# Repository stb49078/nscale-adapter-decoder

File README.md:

# Lokdecoder - Adapter Platinen und DIY Decoder - Spur N

Hier finden sich div. Adapterplatinen und vollständige DIY Lokdecoder auf Basis des (vermutlich eingestellten)
Projekts [Aegaeon](https://github.com/Railstars/Aegaeon) von [Railstars](http://railstars.com/).

Wie dieses Projekt auch, stehen die hier veröffentlichten Designs damit automatisch unter GPLv3.

Die Dekoder wurden leicht angeändert, und verwenden den Motortreiber
[BD623xx](http://rohmfs.rohm.com/en/products/databook/datasheet/ic/motor/dc/bd623x-e.pdf).

## Arnold

**1020/E94**

[NEM-651 Adapter](./loc-decoder/Arnold/1020/NEM-651_Adapter)

## Roco

**1044 alt, z.B. 23242**

[NEM-651 Adapter](./loc-decoder/Roco/1044/NEM-651_Adapter)

[Aegaeon Decoder mit BD62xx und Railcom](./loc-decoder/Roco/1044/Decoder-BD62xx-Railcom)

**BR215, z.B. 2150B**

[NEM-651 Adapter](./loc-decoder/Roco/BR215/NEM-651_Adapter)

**BR 44, z.B. 2106B**

[NEM-651 Adapter](./loc-decoder/Roco/BR44/NEM-651_Adapter)

## Minitrix

**E44**

[NEM-651 Adapter](./loc-decoder/Minitrix/E44/NEM-651_Adapter)

## Spectrum

**GE Dash 8-40CW**

[Aegaeon Decoder mit BD62xx und Railcom](./loc-decoder/Spectrum/GE_Dash_8-40CW/Decoder-BD62xx-Railcom)

# Wagonbeleuchtung mit integriertem Decoder- Spur N

Mit freundlicher Erlaubnis von Hr. Brandt, verwende ich als Basis
für die Wagonbeleuchtung, seinen unter https://www.digital-bahn.de/bau_wald/wald_2v1.htm
veröffentlicheten Spur H0 - Waggon-Licht Dekoder (WaLD) V2.1
Sämtliche Lizenzen für diese Platinen und der darauf verwendeten Software liegen bei digital-bahn.

Diese Platinen werden von meiner Seite nicht zum Verkauf angeboten.
Der Verkauf und/oder Vertrieb eines hier veröffentlichten Designs darf nur unter
Rücksprache mit digital-bahn erfolgen. Copyleft.

Die Anleitung zur Installation der Software und die Schaltungsbeschreibung sind
in der oben genannten Seite zu finden.

Die originale H0-Platine und vorprogrammierte PIC-Controller können im Shop von
digital-bahn unter https://digital-bahn.de/shopping/Waggon-Beleuchtung bezogen werden.  

Folgende Modelle werden aktuell unterstützt:

[Roco - Eurofima z.B. 24270, 24285, uvm.](./wagon-light/Roco/Eurofima)

[Roco - Eilzugwagen / Schlierenwagen z.B. 24280-24281 ](./wagon-light/Roco/Eilzugwagen)

[Minitrix - Eurofima z.B. 3095, 3106, uvm.](./wagon-light/Minitrix/Eurofima)

Für kleinere Wägen gibt es allgemeine Platinen

[Einseite Montage - 50mm * 15mm](./wagon-light/common/50x15)

## Support und Fragen

Bei Fragen, Anregungen und Beschwerden, bitte einfach unter spur.n@stefanbauer.at melden.

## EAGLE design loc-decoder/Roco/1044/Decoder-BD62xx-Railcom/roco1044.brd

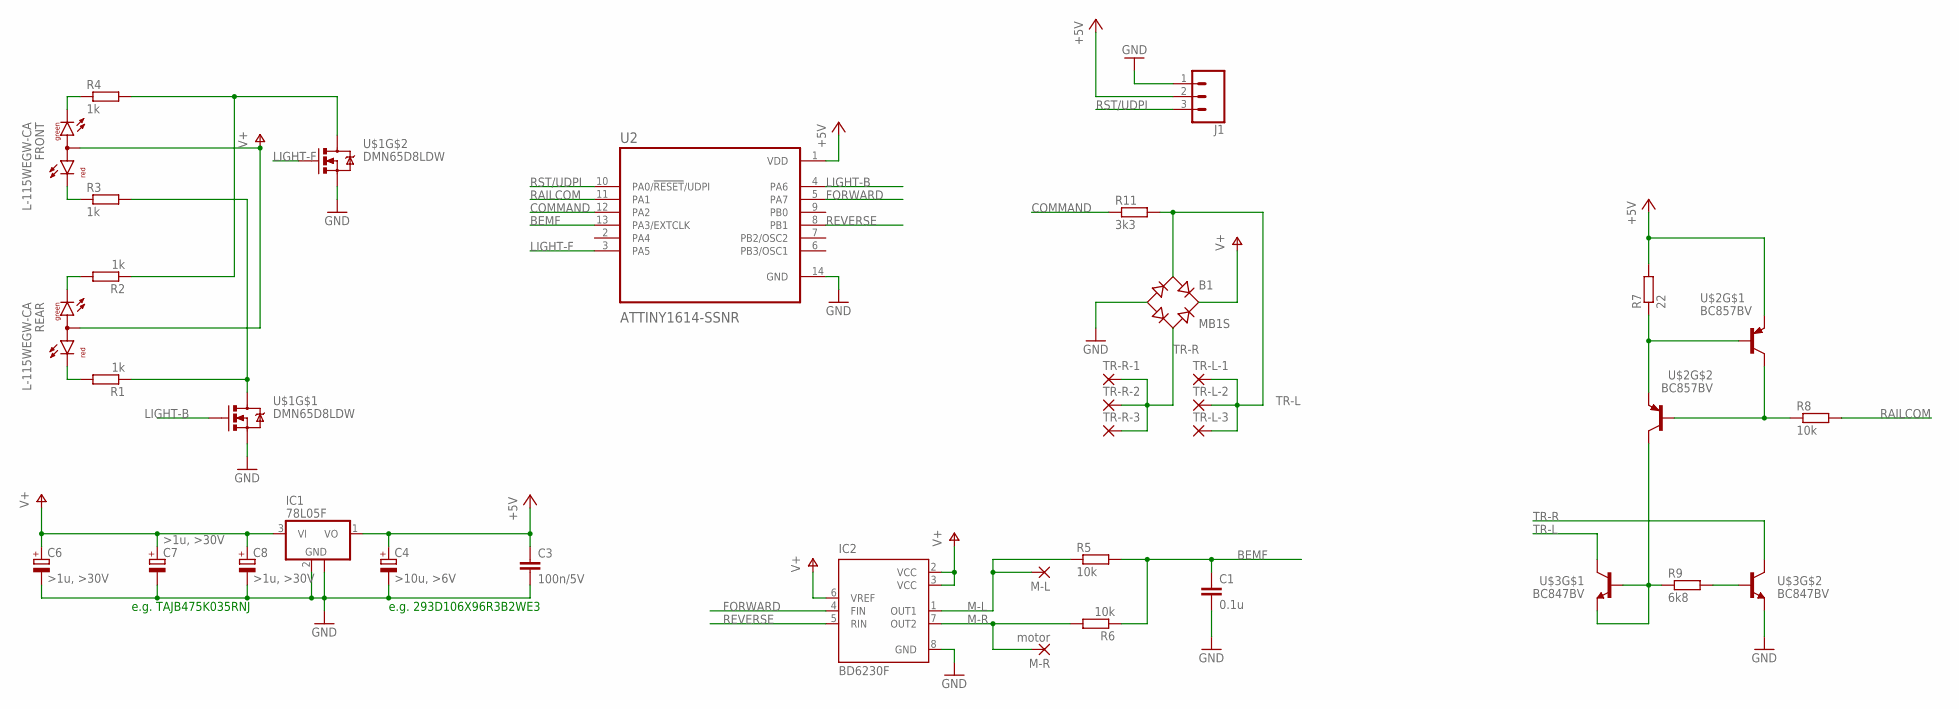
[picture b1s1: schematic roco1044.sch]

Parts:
B1: MB1S; SOIC-4
C1: 0.1u; C0805
C3: 100n/5V; C0805
C4: >10u, >6V; CT3528
C6, C7, C8: >1u, >30V; CT3528
FRONT: L-115WEGW-CA; DUOLED-A-3MM
IC1: 78L05F; SOT89
IC2: BD6230F; SOP8
J1: 455-1750-1-ND; 1X03
M-L: SMD5; SMD2,54-5,08
M-R: motor; SMD2,54-5,08
R1, R2, R3, R4: 1k; R0805
R5, R6, R8: 10k; R0805
R7: 22; R0805
R9: 6k8; R0805
R11: 3k3; R0805
REAR: L-115WEGW-CA; DUOLED-A-3MM
TR-L-1, TR-L-2, TR-L-3: SMD5; SMD2,54-5,08
TR-R-1, TR-R-2, TR-R-3: SMD5; SMD2,54-5,08
U2: ATTINY1614-SSNR; SOIC127P600X175-14N
U$1: DMN65D8LDW; SOT363
U$2: BC857BV; SOT-666
U$3: BC847BV; SOT-666

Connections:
+5V: C3.1, C4.+, IC1.1 (VO), J1.2, R7.2, U2.1 (VDD), U$2.P$1 (E)
BEMF: C1.1, R5.2, R6.1, U2.13 (PA3/EXTCLK)
COMMAND: R11.1, U2.12 (PA2)
FORWARD: IC2.4 (FIN), U2.5 (PA7)
GND: B1.-, C1.2, C3.2, C4.-, C6.-, C7.-, C8.-, IC1.2 (GND), IC1.2@1 (GND), IC2.8 (GND), J1.1, U2.14 (GND), U$1.P$3 (S), U$1.P$6 (S), U$3.P$4 (E)
LIGHT-B: U2.4 (PA6), U$1.P$2 (G)
LIGHT-F: U2.3 (PA5), U$1.P$5 (G)
M-L: IC2.1 (OUT1), M-L.1, R5.1
M-R: IC2.7 (OUT2), M-R.1, R6.2
unnamed: R9.2, U$3.P$5 (B)
unnamed: R9.1, U$2.P$3 (C), U$3.P$1 (E), U$3.P$2 (B)
unnamed: R2.1, R4.2, U$1.P$1 (D)
unnamed: R1.2, REAR.3 (CR)
unnamed: R2.2, REAR.1 (CG)
unnamed: R1.1, R3.2, U$1.P$4 (D)
unnamed: FRONT.3 (CR), R3.1
unnamed: FRONT.1 (CG), R4.1
unnamed: R7.1, U$2.P$2 (B), U$2.P$4 (E)
unnamed: R8.1, U$2.P$5 (B), U$2.P$6 (C)
RAILCOM: R8.2, U2.11 (PA1)
REVERSE: IC2.5 (RIN), U2.8 (PB1)
RST/UDPI: J1.3, U2.10 (PA0/!RESET!/UDPI)
TR-L: B1.~1 (AC1), R11.2, TR-L-1.1, TR-L-2.1, TR-L-3.1, U$3.P$6 (C)
TR-R: B1.~2 (AC2), TR-R-1.1, TR-R-2.1, TR-R-3.1, U$3.P$3 (C)
V+: B1.+, C6.+, C7.+, C8.+, FRONT.2 (A), IC1.3 (VI), IC2.2 (VCC), IC2.3 (VCC), IC2.6 (VREF), REAR.2 (A)

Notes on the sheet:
e.g. TAJB475K035RNJ
e.g. 293D106X96R3B2WE3

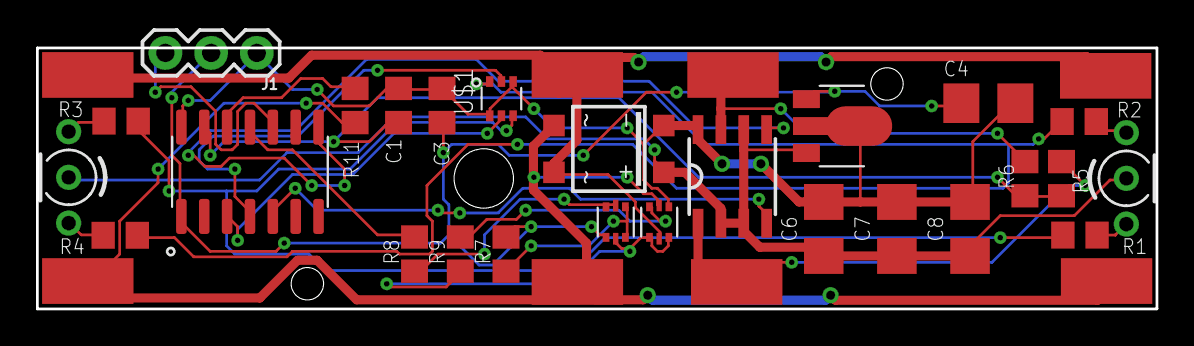
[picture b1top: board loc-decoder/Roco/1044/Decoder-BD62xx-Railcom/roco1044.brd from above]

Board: 2 copper layers, 62.2 x 14.5 mm, 34 parts (0 on the bottom side), 25 nets.

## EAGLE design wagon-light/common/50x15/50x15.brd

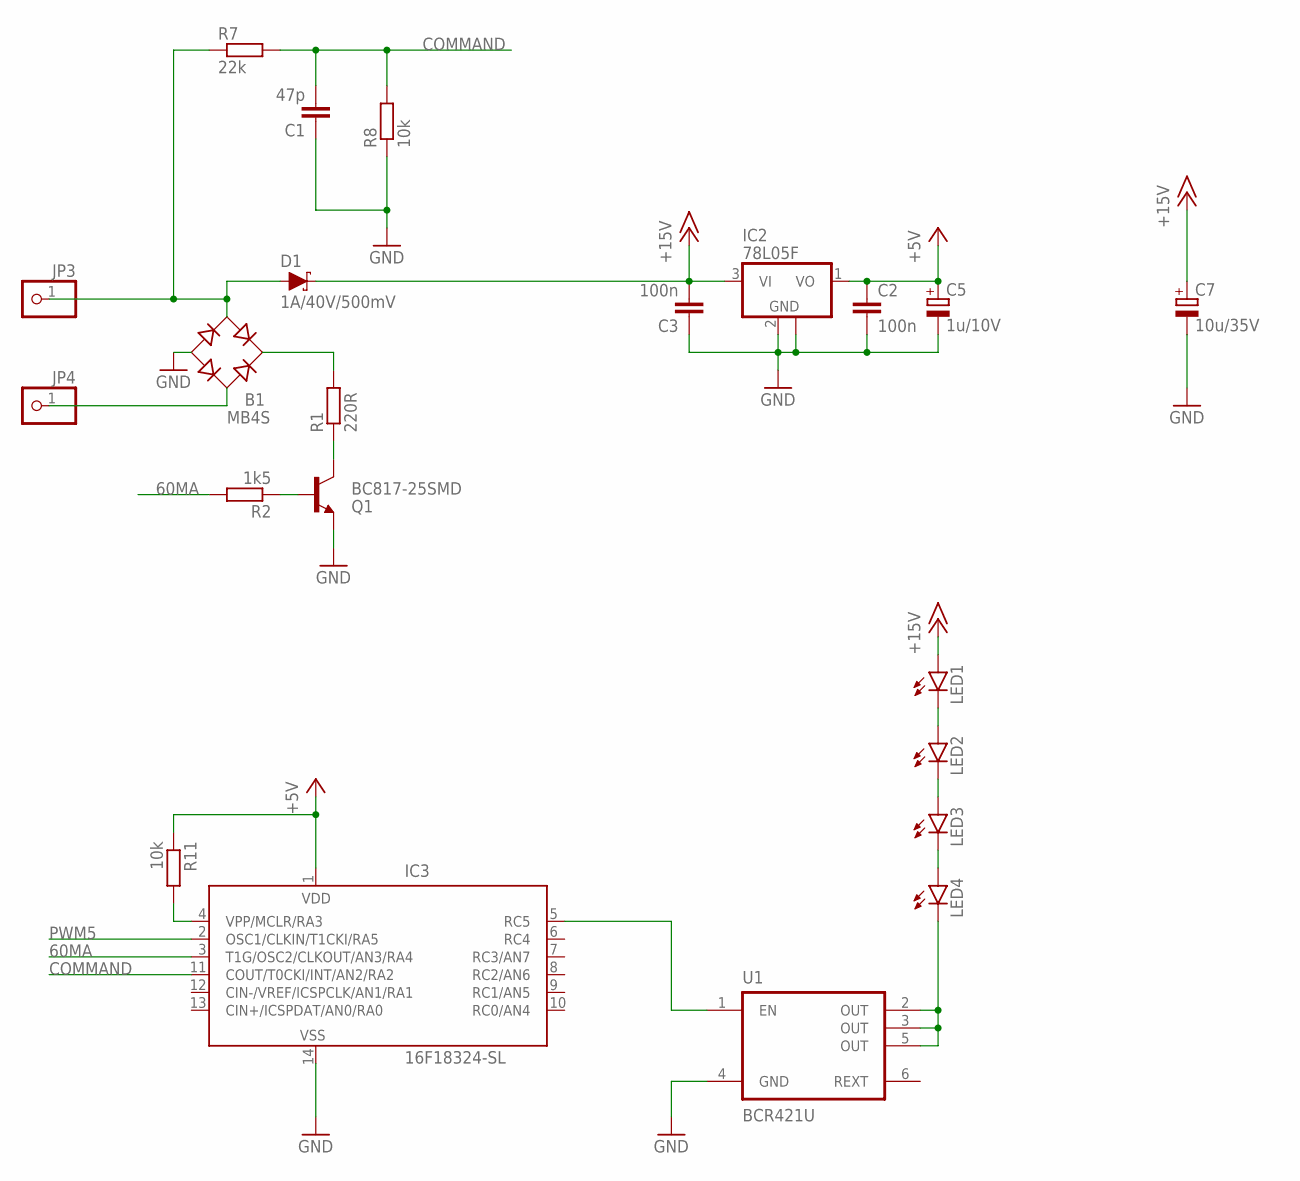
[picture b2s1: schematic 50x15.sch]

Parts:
B1: MB4S; SOIC-4
C1: 47p; C0805
C2, C3: 100n; C3216
C5: 1u/10V; A/3216-18R
C7: 10u/35V; D/7343-31R
D1: 1A/40V/500mV; SMA-DIODE
IC2: 78L05F; SOT89
IC3: 16F18324-SL; SO-14
JP3, JP4: PINHD-1X1; 1X01
LED1, LED2, LED3, LED4: LEDKA-3528ASYC; KA-3528ASYC
Q1: BC817-25SMD; SOT23-BEC
R1: 220R; R1206
R2: 1k5; R1206
R7: 22k; R1206
R8, R11: 10k; R1206
U1: BCR421U; SC74-6

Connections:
60MA: IC3.3 (T1G/OSC2/CLKOUT/AN3/RA4), R2.2
+5V: C2.1, C5.+, IC2.1 (VO), IC3.1 (VDD), R11.1
+15V: C3.2, C7.+, D1.C, IC2.3 (VI), LED1.A
COMMAND: C1.2, IC3.11 (COUT/T0CKI/INT/AN2/RA2), R7.2, R8.2
GND: B1.-, C1.1, C2.2, C3.1, C5.-, C7.-, IC2.2 (GND), IC2.2@1 (GND), IC3.14 (VSS), Q1.E, R8.1, U1.4 (GND)
unnamed: B1.~2 (AC2), JP4.1
unnamed: B1.~1 (AC1), D1.A, JP3.1, R7.1
unnamed: Q1.C, R1.1
unnamed: Q1.B, R2.1
unnamed: B1.+, R1.2
unnamed: IC3.5 (RC5), U1.1 (EN)
unnamed: LED4.C, U1.2 (OUT), U1.3 (OUT), U1.5 (OUT)
unnamed: LED3.C, LED4.A
unnamed: LED2.C, LED3.A
unnamed: LED1.C, LED2.A
unnamed: IC3.4 (VPP/MCLR/RA3), R11.2
PWM5: IC3.2 (OSC1/CLKIN/T1CKI/RA5)

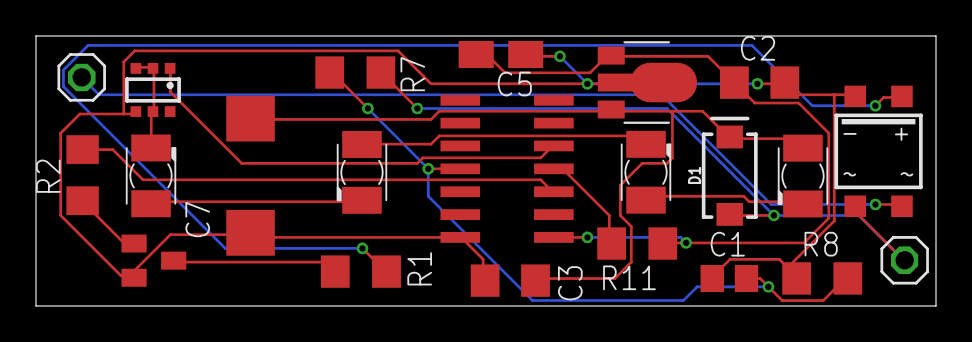
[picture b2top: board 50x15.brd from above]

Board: 2 copper layers, 50.0 x 15.0 mm, 22 parts (0 on the bottom side), 16 nets.

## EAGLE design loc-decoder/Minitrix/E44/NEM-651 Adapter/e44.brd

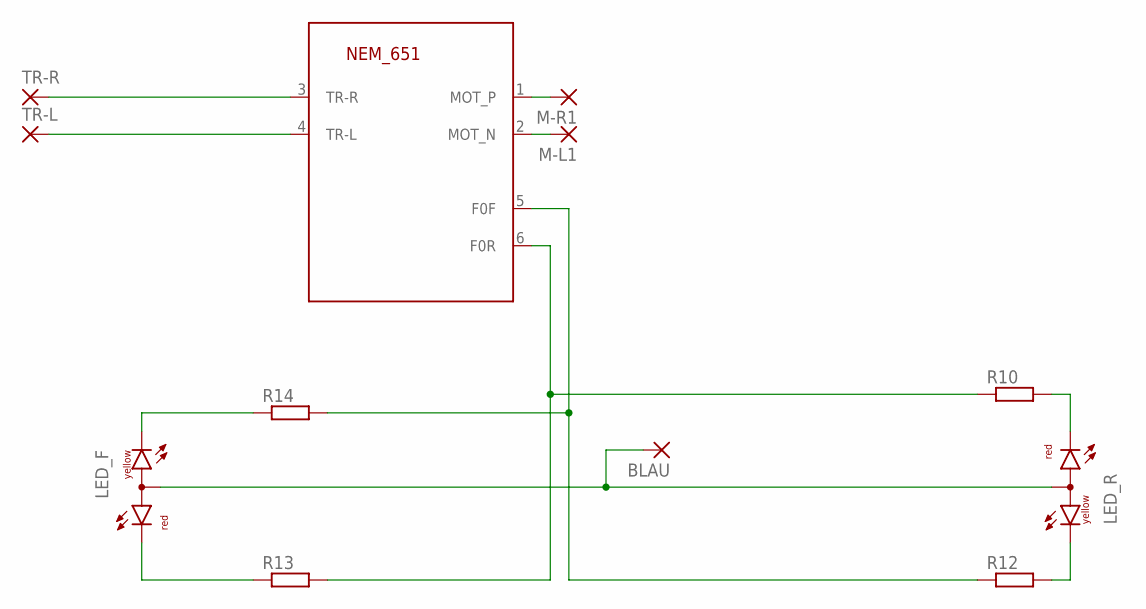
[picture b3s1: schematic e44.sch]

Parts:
651: NEM_651-TS; 53047-06
BLAU: 1,6/0,8
LED_F: DUOLED-RY-A; DUOLED-A-5MM
LED_R: DUOLED-RY-A; DUOLED-A-5MM
M-L1: SMD5; SMD2,54-5,08
M-R1: SMD5; SMD2,54-5,08
R10, R12, R13, R14: R-EU_R1206; R1206
TR-L: SMD5; SMD2,54-5,08
TR-R: SMD5; SMD2,54-5,08

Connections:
unnamed: BLAU.1, LED_F.A, LED_R.A
unnamed: 651.4 (TR-L), TR-L.1
unnamed: 651.3 (TR-R), TR-R.1
unnamed: 651.5 (F0F), R12.1, R14.2
unnamed: LED_R.CR, R10.2
unnamed: LED_R.CX (CY), R12.2
unnamed: 651.6 (F0R), R10.1, R13.2
unnamed: LED_F.CR, R13.1
unnamed: LED_F.CX (CY), R14.1
unnamed: 651.1 (MOT_P), M-R1.1
unnamed: 651.2 (MOT_N), M-L1.1

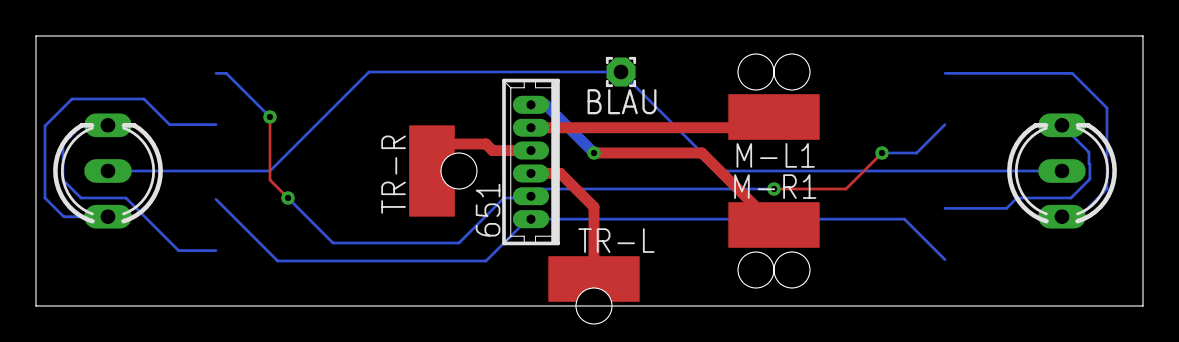
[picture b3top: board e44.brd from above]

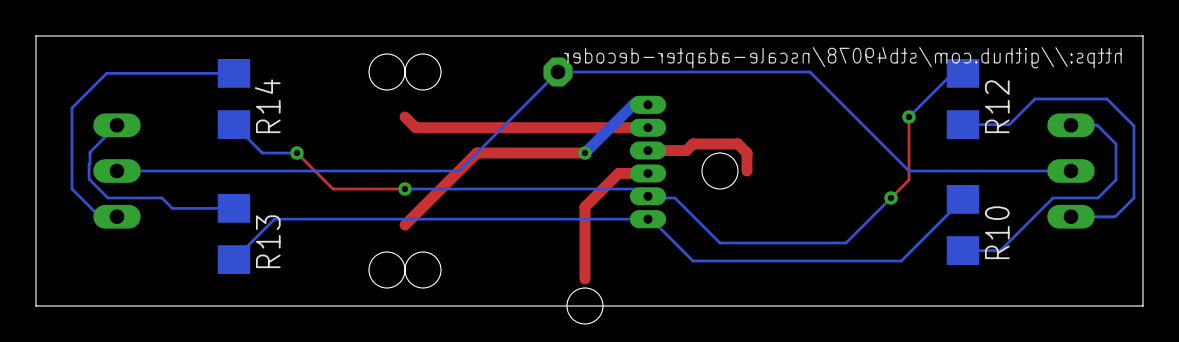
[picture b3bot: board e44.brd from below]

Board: 2 copper layers, 61.5 x 15.0 mm, 12 parts (4 on the bottom side), 11 nets.

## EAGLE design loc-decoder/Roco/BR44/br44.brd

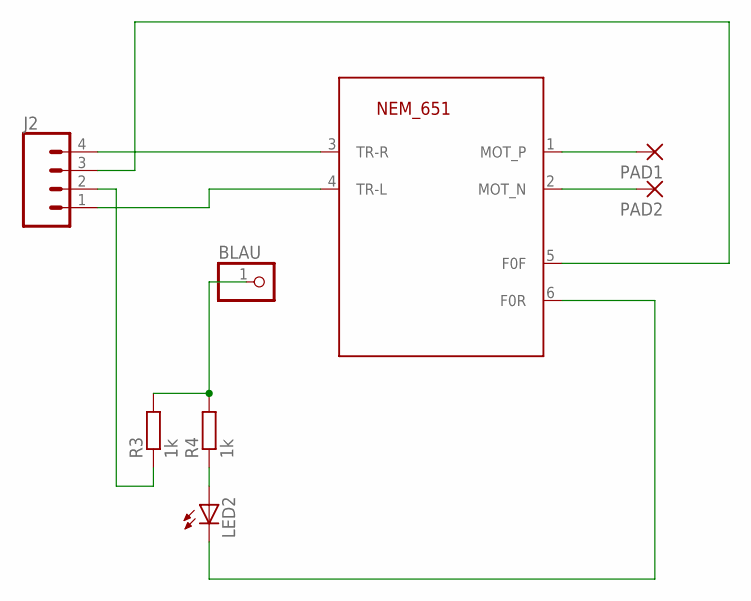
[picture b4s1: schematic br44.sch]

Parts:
BLAU: PINHD-1X1; 1X01
J2: CONN_041X04_NO_SILK; 1X04_NO_SILK
LED2: LED3MM
PAD1, PAD2: SMD5; SMD2,54-5,08
R3, R4: 1k; 0204V
U$1: NEM_651-TS; 53047-06

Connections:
unnamed: PAD1.1, U$1.1 (MOT_P)
unnamed: PAD2.1, U$1.2 (MOT_N)
unnamed: J2.4, U$1.3 (TR-R)
unnamed: J2.1, U$1.4 (TR-L)
unnamed: BLAU.1, R3.2, R4.2
unnamed: LED2.A, R4.1
unnamed: J2.2, R3.1
unnamed: J2.3, U$1.5 (F0F)
unnamed: LED2.K (C), U$1.6 (F0R)

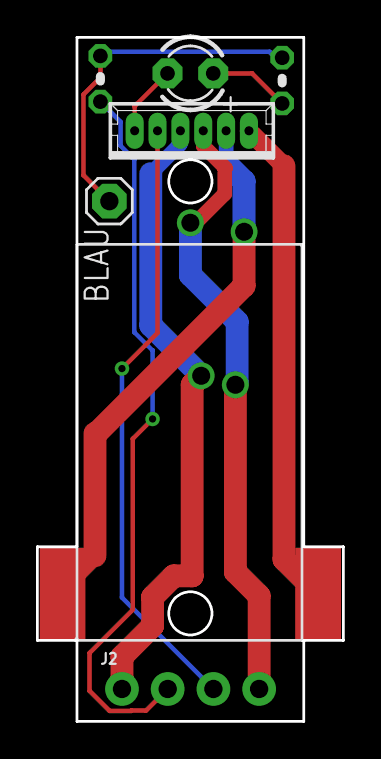
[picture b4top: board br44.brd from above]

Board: 2 copper layers, 17.0 x 38.0 mm, 8 parts (0 on the bottom side), 9 nets.

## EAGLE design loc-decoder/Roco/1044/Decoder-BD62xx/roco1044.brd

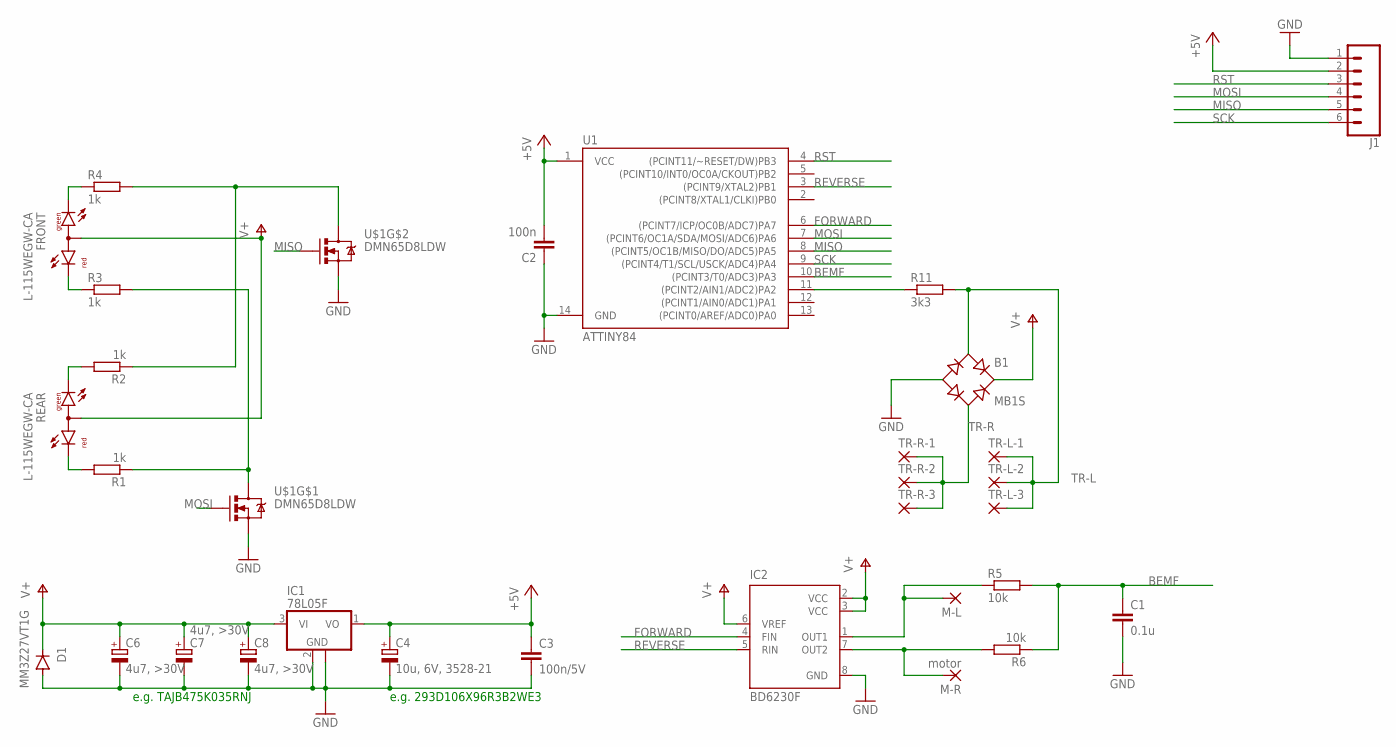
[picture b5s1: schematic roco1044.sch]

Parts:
B1: MB1S; SOIC-4
C1: 0.1u; C0805
C2: 100n; C0805
C3: 100n/5V; C0805
C4: 10u, 6V, 3528-21; CT3528
C6, C7, C8: 4u7, >30V; CT3528
D1: MM3Z27VT1G; SOD323-R
FRONT: L-115WEGW-CA; DUOLED-A-3MM
IC1: 78L05F; SOT89
IC2: BD6230F; SOP8
J1: CONN_061.27MM; 1X06_1.27MM
M-L: SMD5; SMD2,54-5,08
M-R: motor; SMD2,54-5,08
R1, R2, R3, R4: 1k; R0603
R5, R6: 10k; R0603
R11: 3k3; R0603
REAR: L-115WEGW-CA; DUOLED-A-3MM
TR-L-1, TR-L-2, TR-L-3: SMD5; SMD2,54-5,08
TR-R-1, TR-R-2, TR-R-3: SMD5; SMD2,54-5,08
U1: ATTINY84; SO14
U$1: DMN65D8LDW; SOT363

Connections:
+5V: C2.2, C3.1, C4.+, IC1.1 (VO), J1.2, U1.1 (VCC)
BEMF: C1.1, R5.2, R6.1, U1.10 ((PCINT3/T0/ADC3)PA3)
FORWARD: IC2.4 (FIN), U1.6 ((PCINT7/ICP/OC0B/ADC7)PA7)
GND: B1.-, C1.2, C2.1, C3.2, C4.-, C6.-, C7.-, C8.-, D1.A, IC1.2 (GND), IC1.2@1 (GND), IC2.8 (GND), J1.1, U1.14 (GND), U$1.P$3 (S), U$1.P$6 (S)
MISO: J1.5, U1.8 ((PCINT5/OC1B/MISO/DO/ADC5)PA5), U$1.P$5 (G)
MOSI: J1.4, U1.7 ((PCINT6/OC1A/SDA/MOSI/ADC6)PA6), U$1.P$2 (G)
unnamed: IC2.7 (OUT2), M-R.1, R6.2
unnamed: R2.1, R4.2, U$1.P$1 (D)
unnamed: R1.2, REAR.3 (CR)
unnamed: R2.2, REAR.1 (CG)
unnamed: R1.1, R3.2, U$1.P$4 (D)
unnamed: FRONT.3 (CR), R3.1
unnamed: FRONT.1 (CG), R4.1
unnamed: IC2.1 (OUT1), M-L.1, R5.1
unnamed: R11.1, U1.11 ((PCINT2/AIN1/ADC2)PA2)
REVERSE: IC2.5 (RIN), U1.3 ((PCINT9/XTAL2)PB1)
RST: J1.3, U1.4 ((PCINT11/~RESET/DW)PB3)
SCK: J1.6, U1.9 ((PCINT4/T1/SCL/USCK/ADC4)PA4)
TR-L: B1.~1 (AC1), R11.2, TR-L-1.1, TR-L-2.1, TR-L-3.1
TR-R: B1.~2 (AC2), TR-R-1.1, TR-R-2.1, TR-R-3.1
V+: B1.+, C6.+, C7.+, C8.+, D1.C, FRONT.2 (A), IC1.3 (VI), IC2.2 (VCC), IC2.3 (VCC), IC2.6 (VREF), REAR.2 (A)

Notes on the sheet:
e.g. TAJB475K035RNJ
e.g. 293D106X96R3B2WE3

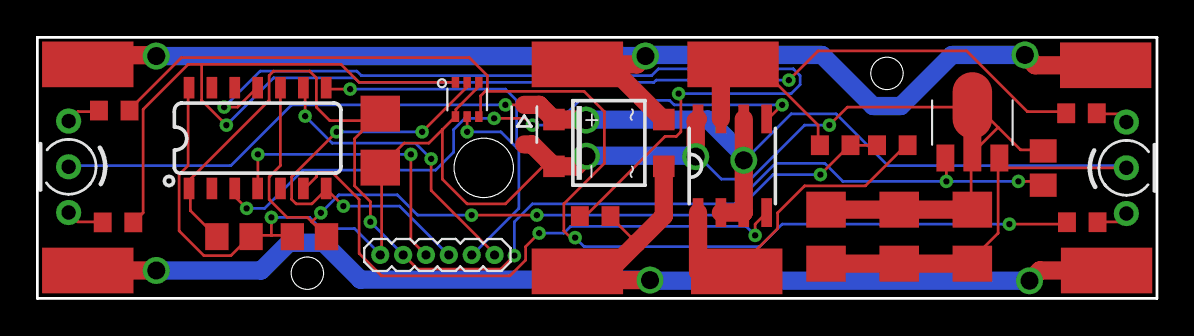
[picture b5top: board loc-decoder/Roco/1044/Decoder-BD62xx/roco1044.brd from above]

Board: 2 copper layers, 62.2 x 14.5 mm, 31 parts (0 on the bottom side), 21 nets.

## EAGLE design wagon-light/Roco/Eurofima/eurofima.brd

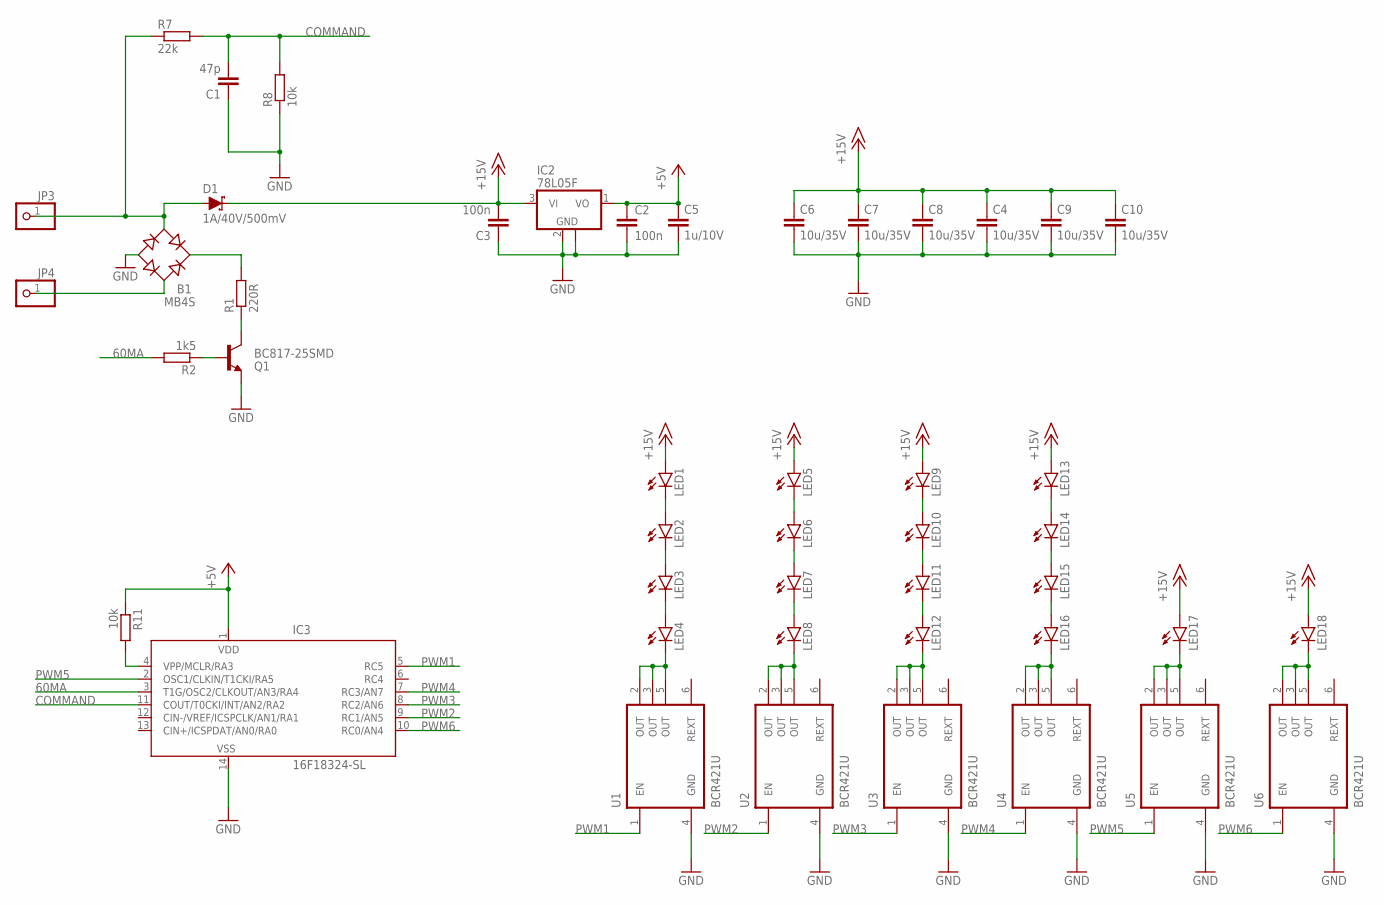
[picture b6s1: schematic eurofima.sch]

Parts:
B1: MB4S; SOIC-4
C1: 47p; C0805
C2, C3: 100n; C3216
C4, C6, C7, C8, C9, C10: 10u/35V; C3216
C5: 1u/10V; C3216
D1: 1A/40V/500mV; SMA-DIODE
IC2: 78L05F; SOT89
IC3: 16F18324-SL; SO-14
JP3, JP4: PINHD-1X1; 1X01
LED1, LED2, LED3, LED4, LED5, LED6, LED7, LED8, LED9, LED10, LED11, LED12, LED13, LED14, LED15, LED16: LEDKA-3528ASYC; KA-3528ASYC
LED17, LED18: LED3MM
Q1: BC817-25SMD; SOT23-BEC
R1: 220R; R1206
R2: 1k5; R1206
R7: 22k; R1206
R8, R11: 10k; R1206
U1, U2, U3, U4, U5, U6: BCR421U; SC74-6

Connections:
60MA: IC3.3 (T1G/OSC2/CLKOUT/AN3/RA4), R2.2
+5V: C2.1, C5.1, IC2.1 (VO), IC3.1 (VDD), R11.1
+15V: C3.2, C4.1, C6.1, C7.1, C8.1, C9.1, C10.1, D1.C, IC2.3 (VI), LED1.A, LED5.A, LED9.A, LED13.A, LED17.A, LED18.A
COMMAND: C1.2, IC3.11 (COUT/T0CKI/INT/AN2/RA2), R7.2, R8.2
GND: B1.-, C1.1, C2.2, C3.1, C4.2, C5.2, C6.2, C7.2, C8.2, C9.2, C10.2, IC2.2 (GND), IC2.2@1 (GND), IC3.14 (VSS), Q1.E, R8.1, U1.4 (GND), U2.4 (GND), U3.4 (GND), U4.4 (GND), U5.4 (GND), U6.4 (GND)
unnamed: B1.~2 (AC2), JP4.1
unnamed: B1.~1 (AC1), D1.A, JP3.1, R7.1
unnamed: Q1.C, R1.1
unnamed: Q1.B, R2.1
unnamed: B1.+, R1.2
unnamed: LED3.C, LED4.A
unnamed: LED7.C, LED8.A
unnamed: LED11.C, LED12.A
unnamed: LED15.C, LED16.A
unnamed: LED16.C, U4.2 (OUT), U4.3 (OUT), U4.5 (OUT)
unnamed: LED14.C, LED15.A
unnamed: LED10.C, LED11.A
unnamed: LED6.C, LED7.A
unnamed: LED2.C, LED3.A
unnamed: LED1.C, LED2.A
unnamed: LED5.C, LED6.A
unnamed: LED9.C, LED10.A
unnamed: LED13.C, LED14.A
unnamed: LED17.K (C), U5.2 (OUT), U5.3 (OUT), U5.5 (OUT)
unnamed: IC3.4 (VPP/MCLR/RA3), R11.2
unnamed: LED18.K (C), U6.2 (OUT), U6.3 (OUT), U6.5 (OUT)
unnamed: LED4.C, U1.2 (OUT), U1.3 (OUT), U1.5 (OUT)
unnamed: LED12.C, U3.2 (OUT), U3.3 (OUT), U3.5 (OUT)
unnamed: LED8.C, U2.2 (OUT), U2.3 (OUT), U2.5 (OUT)
PWM1: IC3.5 (RC5), U1.1 (EN)
PWM2: IC3.9 (RC1/AN5), U2.1 (EN)
PWM3: IC3.8 (RC2/AN6), U3.1 (EN)
PWM4: IC3.7 (RC3/AN7), U4.1 (EN)
PWM5: IC3.2 (OSC1/CLKIN/T1CKI/RA5), U5.1 (EN)
PWM6: IC3.10 (RC0/AN4), U6.1 (EN)

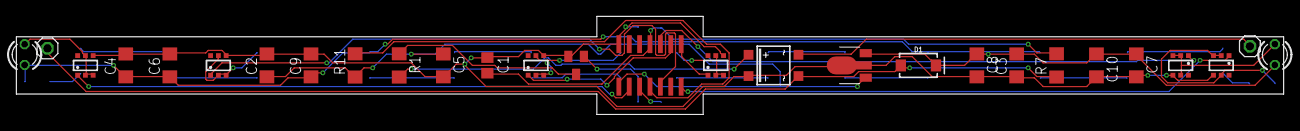
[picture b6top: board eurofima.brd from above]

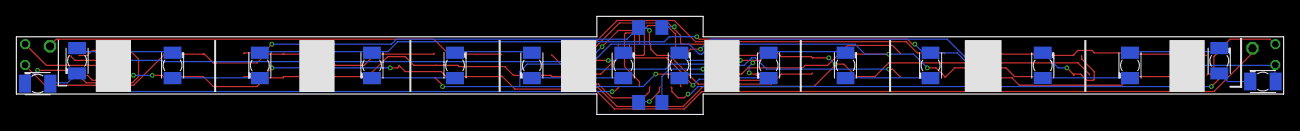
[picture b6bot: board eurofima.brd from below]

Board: 2 copper layers, 155.0 x 12.0 mm, 46 parts (18 on the bottom side), 35 nets.

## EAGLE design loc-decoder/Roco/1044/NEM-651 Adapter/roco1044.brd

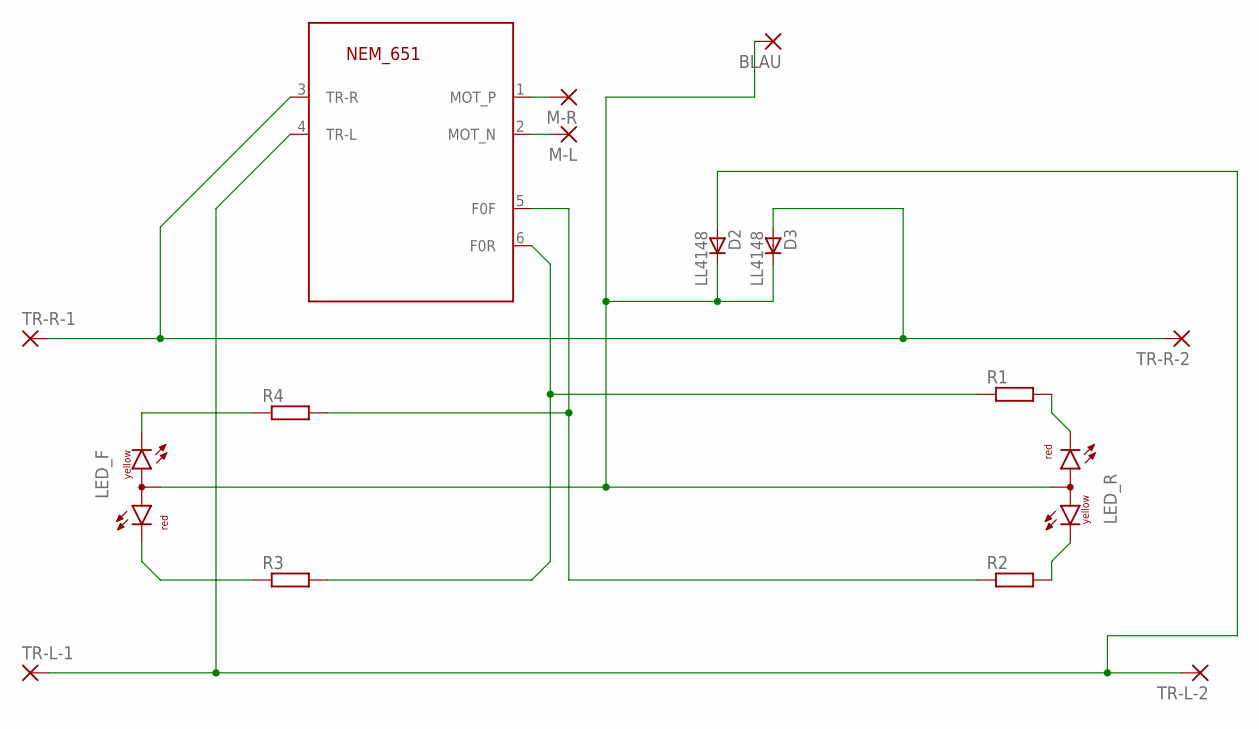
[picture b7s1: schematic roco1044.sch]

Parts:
651: NEM_651-TS; 53047-06
BLAU: 1,6/0,8
D2, D3: LL4148; SOD80_DO213AA_MINIMELF
LED_F: DUOLED-RY-A; DUOLED-A-5MM
LED_R: DUOLED-RY-A; DUOLED-A-5MM
M-L: SMD5; SMD2,54-5,08
M-R: SMD5; SMD2,54-5,08
R1, R2, R3, R4: R-EU_R1206; R1206
TR-L-1, TR-L-2: SMD5; SMD2,54-5,08
TR-R-1, TR-R-2: SMD5; SMD2,54-5,08

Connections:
unnamed: BLAU.1, D2.C, D3.C, LED_F.A, LED_R.A
unnamed: 651.4 (TR-L), D2.A, TR-L-1.1, TR-L-2.1
unnamed: 651.3 (TR-R), D3.A, TR-R-1.1, TR-R-2.1
unnamed: 651.1 (MOT_P), M-R.1
unnamed: 651.5 (F0F), R2.1, R4.2
unnamed: LED_R.CR, R1.2
unnamed: LED_R.CX (CY), R2.2
unnamed: 651.6 (F0R), R1.1, R3.2
unnamed: LED_F.CR, R3.1
unnamed: LED_F.CX (CY), R4.1
unnamed: 651.2 (MOT_N), M-L.1

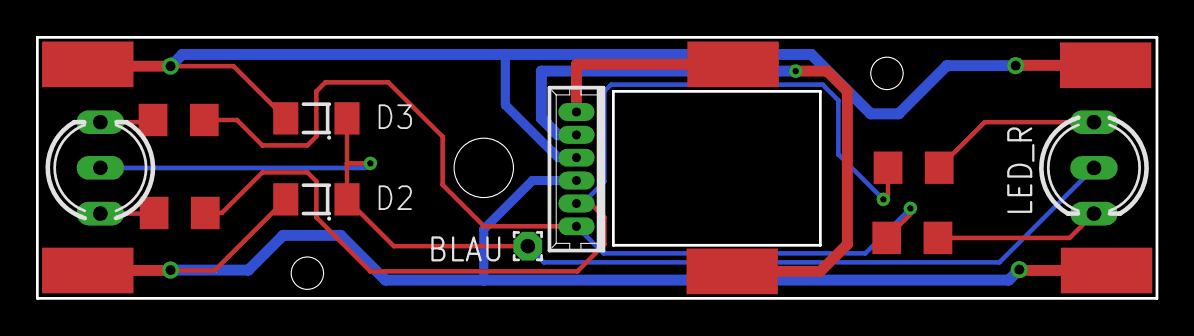
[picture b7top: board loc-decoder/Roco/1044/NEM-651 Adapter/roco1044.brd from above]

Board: 2 copper layers, 62.2 x 14.5 mm, 16 parts (0 on the bottom side), 11 nets.

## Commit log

2020-01-15 first
2020-01-19 roco eurofima
2020-01-19 legacy loc decoder
2020-01-19 misc
2020-08-12 changed dir structure
2021-01-11 BR44 nut soldermask correction

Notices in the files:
parts and their libraries:
SparkFun-Connectors: Licensing: Creative Commons ShareAlike 4.0 International - https://creativecommons.org/licenses/by-sa/4.0
